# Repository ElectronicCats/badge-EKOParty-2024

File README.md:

# Badge EKO Party 2024
Badge Oficial de EKOPARTY 2024

## Getting started

1. Connect Badge via USB to your computer.
2. Open the serial port indicated for the badge on your computer through a program such as Arduino IDE, Putty or Screen at 115200 bauds.
3. The badge text should appear in the terminal.

## Tecnologia

- ESP32C6
- LEDs neopixel
- USB
- LoRa
- Buzzer
- OLED

## How to build the firmware

Check the [Developer guide](./firmware/README.md) to learn how to build the firmware from scratch.

## Gratitude
Do you want to say thank you? Tag these companies on social networks and show them your badge, thanks to them it is possible

- [ElectronicCats](https://electroniccats.com/)

## License

Electronic Cats invests time and resources providing this open source design, please support Electronic Cats and open-source hardware by purchasing products from Electronic Cats!

Designed by Electronic Cats.

Hardware released under an CERN Open Hardware Licence v1.2. See the LICENSE_HARDWARE file for more information.

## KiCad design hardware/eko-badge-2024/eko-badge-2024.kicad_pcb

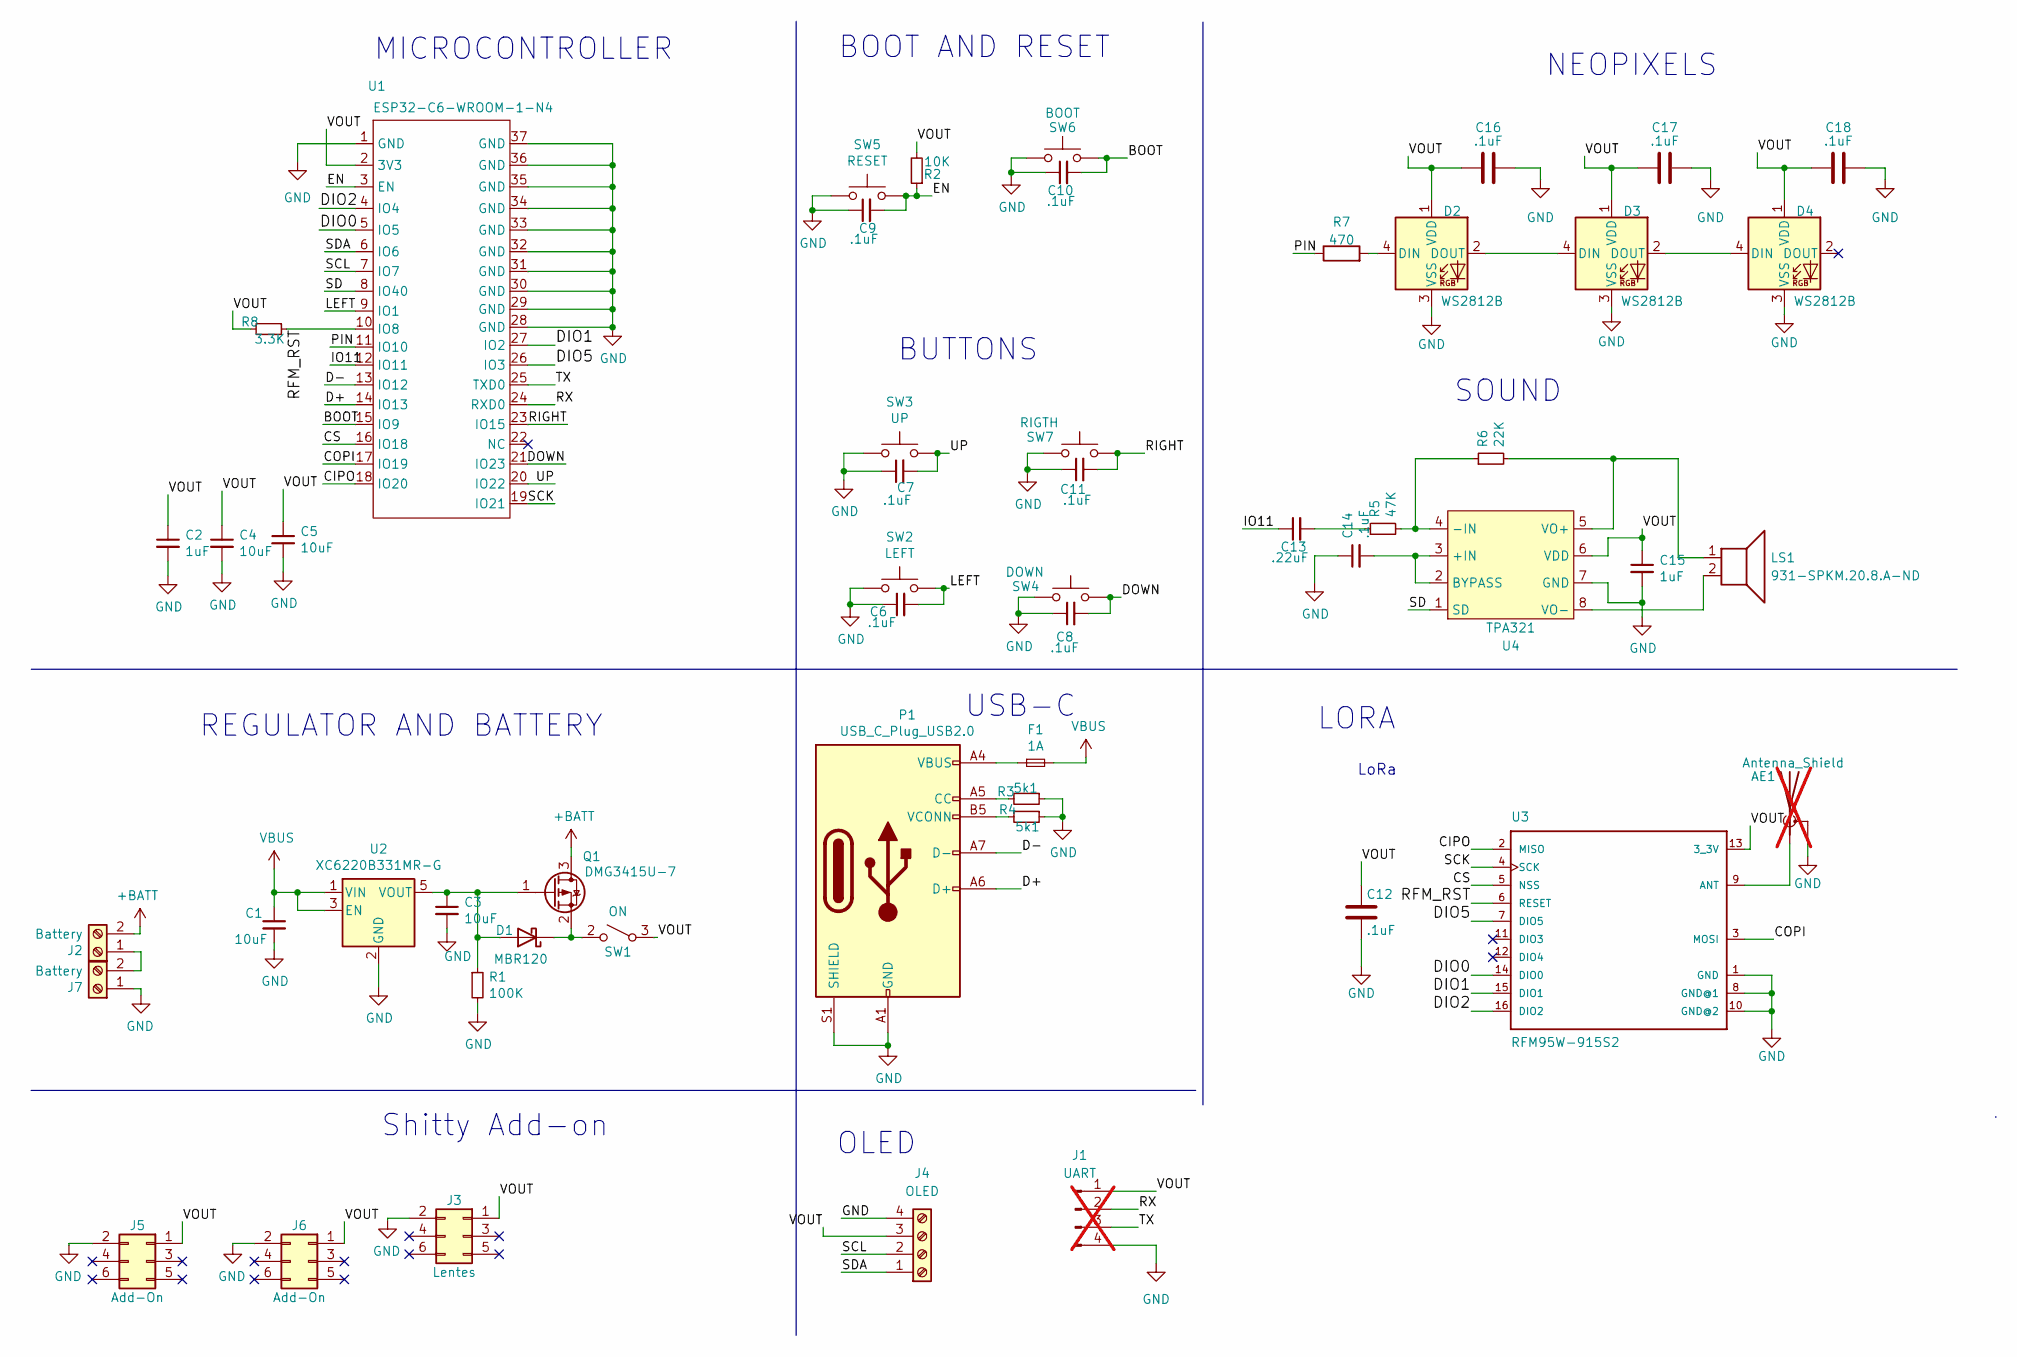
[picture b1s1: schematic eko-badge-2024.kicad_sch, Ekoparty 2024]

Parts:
AE1: Antenna_Shield; PinHeader_1x01_P2.54mm_Vertical; LCSC# C2913580; not fitted
C1, C3, C4, C5: 10uF; C_0603_1608Metric; LCSC# C85713
C2, C15: 1uF; C_0603_1608Metric; LCSC# C15849
C6, C7, C8, C9, C10, C11, C12, C14, C16, C17, C18: .1uF; C_0603_1608Metric; LCSC# C478888
C13: .22uF; C_0603_1608Metric; LCSC# C161213
D1: MBR120; D_SOD-123F; LCSC# C130880
D2, D3, D4: WS2812B; LED_WS2812B-Mini_PLCC4_3.5x3.5mm; LCSC# C527089
F1: 1A; Fuse_0805_2012Metric; LCSC# C2649564
J1: UART; PinHeader_1x04_P2.54mm_Vertical; not fitted
J2, J7: Battery; BH-AA-A1AJ020; LCSC# C5290181
J3: Lentes; HARWIN_M20-7810345
J4: OLED; Display OLED 128 x32
J5, J6: Add-On; PinSocket_2x03_P2.54mm_Vertical_SMD; LCSC# C3975148
LS1: 931-SPKM.20.8.A-ND; PinHeader_1x02_P2.54mm_Vertical
P1: USB_C_Plug_USB2.0; C393939; LCSC# C393939
Q1: DMG3415U-7; SOT-23; LCSC# C96616
R1: 100K; R_0603_1608Metric; LCSC# C25803
R2: 10K; R_0603_1608Metric; LCSC# C217281
R3, R4: 5k1; R_0603_1608Metric; LCSC# C191782
R5: 47K; R_0603_1608Metric; LCSC# C25819
R6: 22K; R_0603_1608Metric; LCSC# C912502
R7: 470; R_0603_1608Metric; LCSC# C103661
R8: 3.3K; R_0603_1608Metric; LCSC# C403480
SW1: ON; MSK12C02; LCSC# C431540
SW2: LEFT; SW_SPST_TL3342; LCSC# C318889
SW3: UP; SW_SPST_TL3342; LCSC# C318889
SW4: DOWN; SW_SPST_TL3342; LCSC# C318889
SW5: RESET; SW_SPST_TL3342; LCSC# C318889
SW6: BOOT; SW_SPST_TL3342; LCSC# C318889
SW7: RIGTH; SW_SPST_TL3342; LCSC# C318889
U1: ESP32-C6-WROOM-1-N4; XCVR_ESP32-C6-WROOM-1-N8
U2: XC6220B331MR-G; SOT-23-5; LCSC# C86534
U3: RFM95W-915S2; HOPERF_RFM9XW_SMD
U4: TPA321; SOP-8_3.9x4.9mm_P1.27mm; LCSC# C2873032

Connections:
+BATT: J2.2, Q1.3 (D)
/BOOT: C10.2, SW6.2, U1.15 (IO9)
/CIPO: U1.18 (IO20), U3.2 (MISO)
/COPI: U1.17 (IO19), U3.3 (MOSI)
/CS: U1.16 (IO18), U3.5 (NSS)
/D+: P1.A6 (D+), U1.14 (IO13)
/D-: P1.A7 (D-), U1.13 (IO12)
/DIO0: U1.5 (IO5), U3.14 (DIO0)
/DIO1: U1.27 (IO2), U3.15 (DIO1)
/DIO2: U1.4 (IO4), U3.16 (DIO2)
/DIO5: U1.26 (IO3), U3.7 (DIO5)
/DOWN: C8.2, SW4.2, U1.21 (IO23)
/EN: C9.2, R2.1, SW5.2, U1.3 (EN)
/IO11: C13.1, U1.12 (IO11)
/LEFT: C6.2, SW2.2, U1.9 (IO1)
/PIN: R7.1, U1.11 (IO10)
/RFM_RST: R8.1, U1.10 (IO8), U3.6 (RESET)
/RIGHT: C11.2, SW7.2, U1.23 (IO15)
/RX: J1.2, U1.24 (RXD0)
/SCK: U1.19 (IO21), U3.4 (SCK)
/SCL: J4.2, U1.7 (IO7)
/SD: U1.8 (IO40), U4.1 (SD)
/SDA: J4.1, U1.6 (IO6)
/TX: J1.3, U1.25 (TXD0)
/UP: C7.2, SW3.2, U1.20 (IO22)
/VOUT: C2.1, C4.1, C5.1, C12.1, C15.1, C16.2, C17.2, C18.2, D2.1 (VDD), D3.1 (VDD), D4.1 (VDD), J1.1, J3.1, J4.3, J5.1, J6.1, R2.2, R8.2, SW1.3 (A), U1.2 (3V3), U3.13 (3_3V), U4.6 (VDD)
GND: AE1.2 (Shield), C1.2, C2.2, C3.2, C4.2, C5.2, C6.1, C7.1, C8.1, C9.1, C10.1, C11.1, C12.2, C14.1, C15.2, C16.1, C17.1, C18.1, D2.3 (VSS), D3.3 (VSS), D4.3 (VSS), J1.4, J3.2, J4.4, J5.2, J6.2, J7.1, P1.A1 (GND), P1.A12 (GND), P1.B1 (GND), P1.B12 (GND), P1.S1 (SHIELD), R1.2, R3.1, R4.1, SW2.1, SW3.1, SW4.1, SW5.1, SW6.1, SW7.1, U1.1 (GND), U1.28 (GND), U1.29 (GND), U1.30 (GND), U1.31 (GND), U1.32 (GND), U1.33 (GND), U1.34 (GND), U1.35 (GND), U1.36 (GND), U1.37 (GND), U2.2 (GND), U3.1 (GND), U3.8 (GND@1), U3.10 (GND@2), U4.7 (GND)
unnamed: AE1.1 (A), U3.9 (ANT)
unnamed: C13.2, R5.1
unnamed: C3.1, D1.2 (A), Q1.1 (G), R1.1, U2.5 (VOUT)
unnamed: D1.1 (K), Q1.2 (S), SW1.2 (B)
unnamed: D2.4 (DIN), R7.2
unnamed: D2.2 (DOUT), D3.4 (DIN)
unnamed: D3.2 (DOUT), D4.4 (DIN)
unnamed: F1.1, P1.A4 (VBUS), P1.A9 (VBUS), P1.B4 (VBUS), P1.B9 (VBUS)
unnamed: J2.1, J7.2
unnamed: P1.A5 (CC), R3.2
unnamed: P1.B5 (VCONN), R4.2
unnamed: C14.2, U4.2 (BYPASS), U4.3 (+IN)
unnamed: R5.2, R6.1, U4.4 (-IN)
unnamed: LS1.1, R6.2, U4.5 (VO+)
unnamed: LS1.2, U4.8 (VO-)
VBUS: C1.1, F1.2, U2.1 (VIN), U2.3 (EN)

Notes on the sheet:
MICROCONTROLLER
LoRa
OLED
USB-C
BUTTONS
SOUND
LORA
NEOPIXELS
REGULATOR AND BATTERY
Shitty Add-on
BOOT AND RESET

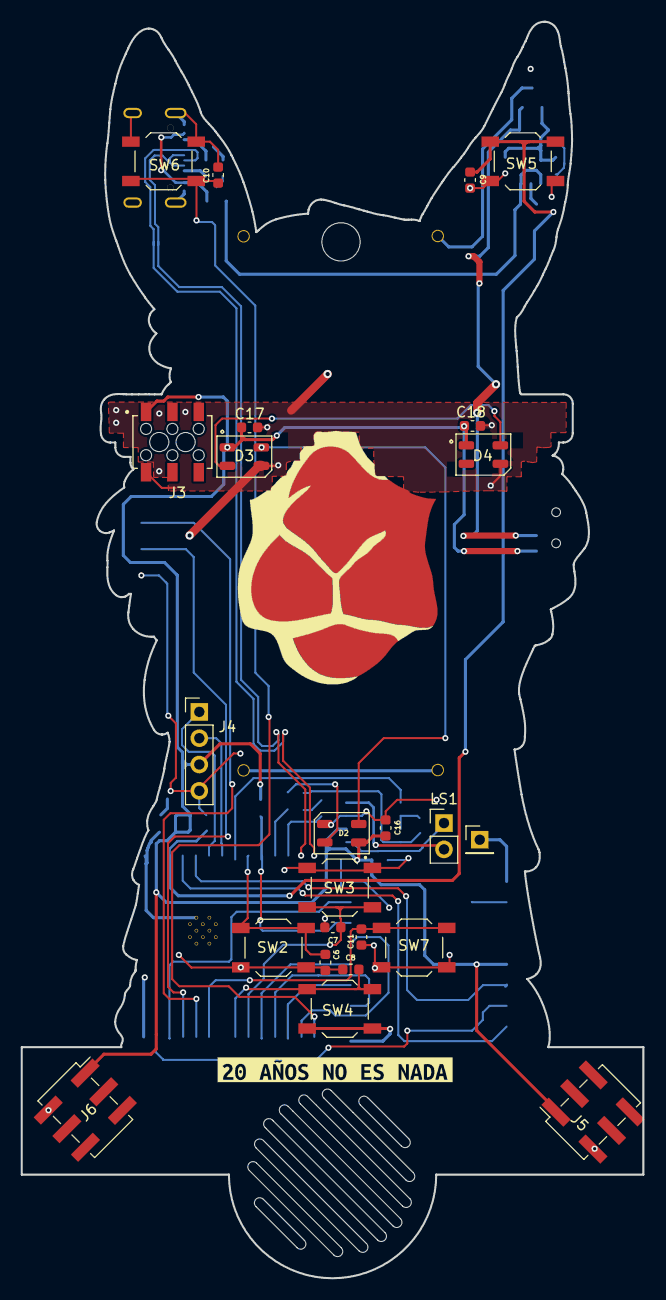
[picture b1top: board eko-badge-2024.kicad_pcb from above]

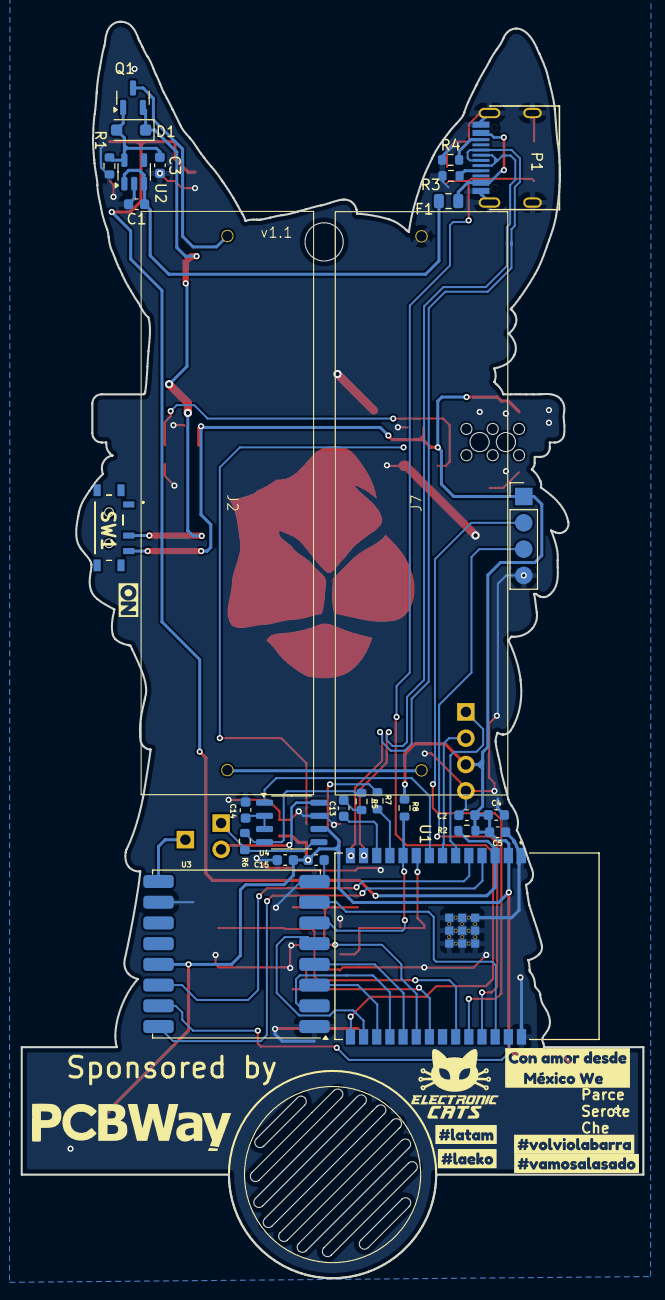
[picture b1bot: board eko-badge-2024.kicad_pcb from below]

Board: 2 copper layers, 60.0 x 121.3 mm, 61 parts (35 on the bottom side), 43 nets.

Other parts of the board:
Ref**: Val**; llama mask flaca
kibuzzard-66BD383E: G***; kibuzzard-66BD383E
kibuzzard-66D7A032: G***; kibuzzard-66D7A032
kibuzzard-66D79F5F: G***; kibuzzard-66D79F5F
kibuzzard-66D79F47: G***; kibuzzard-66D79F47
kibuzzard-66D79F90: G***; kibuzzard-66D79F90
kibuzzard-66D79FA5: G***; kibuzzard-66D79FA5
kibuzzard-66E4B147: G***; kibuzzard-66E4B147

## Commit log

2024-04-29 feat(hw): init schematic 20 años de la eko!
2024-05-15 feat: Update README.md
2024-05-31 feat(Hw):Update_PCB_Added_LoRa_And_Sound_Module
2024-07-23 feat(Hw):Added_Lentes_project
2024-07-25 feat(Hw):Added_First_Route
2024-08-01 feat(Hw):Update_Layer_Distribution
2024-08-14 feat(Hw):Added_Shitty_Add-on
2024-08-15 feat(Hw):Update_Lentes
2024-08-15 feat(Hw): Update lentes
2024-08-15 feeat(Hw):Added_New_Cut
2024-08-15 feat(Hw): Change shitty add on
2024-08-15 feat(Hw):Added_details
2024-08-16 feat(Hw): Update route
2024-08-16 feat(Hw): Update PCB
2024-08-16 feat(Hw): Update BOM
2024-08-16 fix(hw): update RFM95 module version to 915
2024-09-03 feat(Hw):Added_Speaker_Holes
2024-09-03 feat(hw): add logo pcbway and EC
2024-09-03 feat: update labels
2024-09-05 feat(Hw):Update_Connector_Pinsocket
2024-09-13 feat(Hw):Update_BoM
2024-09-13 feat(Hw):Added_Lentes_BoM
2024-09-17 feat: add logo pcbway
2024-09-23 fix(Hw):Moved_Speaker_Connector
2024-10-08 feat: Add first core
2024-10-09 feat: Add neopixels
2024-10-09 feat: iBeacon scanner detects villages uuids
2024-10-10 feat: Change Lora lib
2024-10-10 feat: add pre-commit-config
2024-10-10 refactor: set correct village names
2024-10-10 feat: add pre commit config
2024-10-10 feat: add neopixels
    avoid merge conflicts
2024-10-10 refactor: code format
2024-10-10 feat: ibeacon modularized
2024-10-10 feat: on village detected function
2024-10-10 feat: set village colors
2024-10-10 feat: nearest village selection & beacons timout
2024-10-11 feat: Lora validation
2024-10-11 feat: Start history
2024-10-11 feat: Add sound
2024-10-14 feat: Add history
2024-10-16 feat: Pre-Commit config
2024-10-16 refactor: format code
2024-10-16 feat: toast base
2024-10-16 feat: toast cooldown time in flash
2024-10-17 feat: Add Exit menu from finished history
2024-10-17 refactor: neopixels task notification support
2024-10-17 feat: village colors in task
2024-10-17 feat: Fix neopixeles animation
2024-10-17 feat: llamaneitor animation on village exit
2024-10-18 feat: Add inventary
2024-10-18 feat: precommit format
2024-10-18 feat: Enable Lora Sounds
2024-10-18 feat: refactor & inventory base functions
2024-10-19 fix: Neopixeles run
2024-10-19 feat: Add Mision
2024-10-19 feat: Add Mission 2
    - I Will back
2024-10-19 feat: Add code selector
2024-10-21 fix: character selection
2024-10-21 fix: matrix refresh after incorrect code
2024-10-21 feat: show character profile
2024-10-21 feat: character selection
2024-10-22 refactor: toast dir
2024-10-22 feat: flame menu bases
2024-10-22 feat: Add lora notify
2024-10-22 feat: toast triggered form flame menu
2024-10-22 feat: flame animation
2024-10-22 feat: Fix neopixels animation
2024-10-22 feat: Fix infinite left
2024-10-24 refactor: hide locked item names
2024-10-24 feat: set current llamaneitor scene
2024-10-24 feat: show village name on screen
2024-10-24 feat: avoid village alert on submenus
2024-10-25 feat: boss alert & volver chiptune on toast
2024-10-28 feat: Add Mission
2024-10-28 feat: feed flame on village detected
2024-10-28 feat: weaken flame by button pulses
2024-10-28 feat: Add Yes we Hack and Mission unlock
2024-10-28 feat: flame feedback improved
2024-10-28 feat: Add neopixel limit
2024-10-29 feat: add sitting michi image
2024-10-29 feat: add solderin iron image
2024-10-29 feat: add luchador face image
2024-10-29 feat: add fathoms' images
2024-10-29 feat: Add unlock mission 1
2024-10-29 feat: add kitty medal image
2024-10-29 feat: chiptune struct to play sounds
2024-10-29 feat: fathoms bitmap
2024-10-29 feat: items bitmaps
2024-10-29 feat: villages almanac
2024-10-30 feat: Add History sounds
2024-10-30 feat: Add Lora validations
2024-10-30 fix: remove ln in items keycode
2024-10-30 feat: Fix mission storage
2024-10-30 feat: Verif missions
2024-10-30 fix: playing soundtraks
2024-10-30 feat: character descriptions
2024-10-31 feat: Start refactor missions
    - Add two paths for mission 1
2024-10-31 feat: add EKO about file
2024-10-31 refactor: update about information
2024-10-31 feat: get 3rd cat when almanac is completed
2024-10-31 feat: new village unlocked
2024-10-31 feat: add 3rd cat instruction
2024-10-31 feat: add inventory descriptions
2024-10-31 feat: Add Mission 2 interactions
2024-11-01 feat: inventory items
2024-11-01 feat: Improve Mission 2
2024-11-05 feat: Finish mission 2
2024-11-05 feat: Add mission lib
2024-11-05 feat: Fix sounds
2024-11-08 feat: Change Patagon Village
2024-11-11 feat: add
2024-11-11 feat: Fix wifi module
2024-11-12 feat: Disable apps
2024-12-27 docs: update setup instructions
2025-01-29 feat: Create LICENSE_HARDWARE.md
